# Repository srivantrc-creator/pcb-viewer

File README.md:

# Chalem Circuit Lab

An interactive toolkit for linear circuit analysis — the kind of tool
you'd actually use to check homework, not just something to put on a
resume. Covers everything from basic resistive DC circuits through AC
phasor analysis, first-order transients, diodes, and MOSFETs.

## What's in it

- **Circuit Builder** — enter a netlist (elements between labeled nodes,
  node 0 = ground), and it solves for every node voltage and element
  current/power using Modified Nodal Analysis. The schematic redraws
  itself as a textbook-style orthogonal diagram — resistor zigzags,
  source circles, an IEEE ground symbol, and labeled current-reference
  arrows — for any netlist you build, not just a fixed example. The same
  solver runs in DC mode and AC/phasor mode (R/L/C as complex impedances
  at a chosen frequency) — DC is just AC at ω = 0.
  - **Thevenin/Norton tab**: pick two "port" nodes, get V_th, R_th/Z_th, and I_N.
  - **Superposition tab**: see each independent source's individual
    contribution to a node voltage, with the others zeroed.
- **First-Order Calculator** — RC/RL step response: time constant, the
  general solution equation, and a plotted response curve.
- **Magnetics Calculator** — coupling coefficient k, ideal transformer
  turns ratio, and reflected impedance.
- **Diode Calculator** — solves the standard series
  source+resistor+diode circuit with the constant-voltage-drop model,
  showing the assume-ON-then-check worked steps.
- **MOSFET Calculator** — bias-point region check (cutoff/triode/
  saturation), g_m and r_o, and common-source amplifier gain.

## Why not one generic circuit simulator for everything?

Diodes and MOSFETs are nonlinear, so "just solve it" isn't really a thing
the way it is for a linear resistor network — those sections are built
around specific hand-analysis methods (constant-voltage-drop, square-law
region checks) instead of pretending to be SPICE.

## Running locally

```bash
npm install
npm run dev
```

## Verifying the solver

The Modified Nodal Analysis engine has a standalone numeric test suite
(voltage/current dividers, Thevenin equivalents, superposition, and an AC
RC divider checked against hand-calculated impedance values):

```bash
npx tsx scripts/verify-circuit.ts
```

## Deploying to Vercel

Standard Vite + React + TypeScript app — Vercel auto-detects everything.
Push to GitHub, import the repo at vercel.com/new, deploy:

```bash
npm install -g vercel
vercel --prod
```

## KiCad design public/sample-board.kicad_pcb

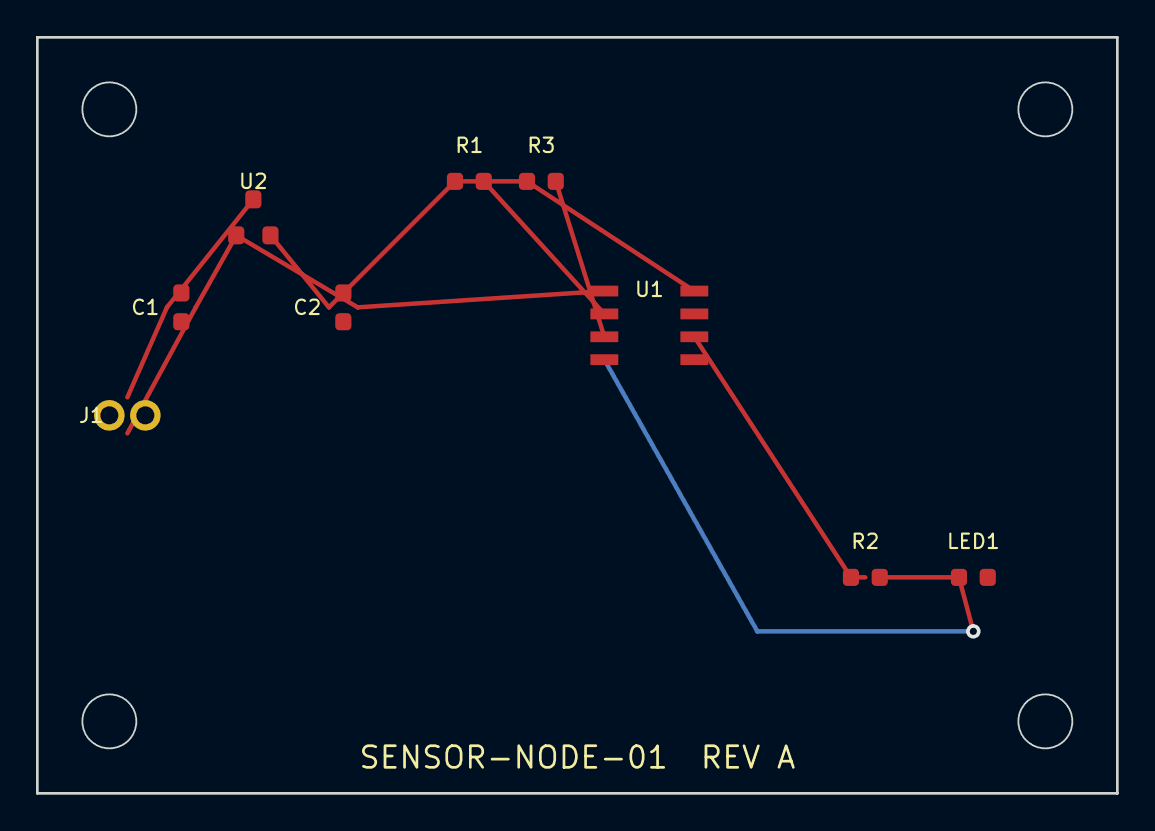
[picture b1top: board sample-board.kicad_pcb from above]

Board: 2 copper layers, 60.0 x 42.0 mm, 9 parts (0 on the bottom side), 7 nets.

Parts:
C1, C2: 1uF; C_0603_1608Metric
J1: PWR_IN; JST_PH_S2B-PH-K_1x02_P2.00mm_Vertical
LED1: Green; LED_0603_1608Metric
R1, R3: 4.7k; R_0603_1608Metric
R2: 330; R_0603_1608Metric
U1: ATtiny-Sensor-MCU; SOIC-8_3.9x4.9mm_P1.27mm
U2: AP2112K-3.3; SOT-23

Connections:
GND: C1.2, C2.2, J1.2, LED1.2, U1.1, U2.1
LED_A: LED1.1, R2.2
LED_CTRL: R2.1, U1.5
SCL: R3.2, U1.3
SDA: R1.2, U1.2
VCC: C2.1, R1.1, R3.1, U1.8, U2.2
VIN: C1.1, J1.1, U2.3
